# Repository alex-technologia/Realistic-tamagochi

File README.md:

# Realistic-tamagochi
A tamagochi but much more realistically accurate 
My parents have always been pretty negative about having a pet. To them i do not have the responsibility to keep one. Ive heard tamogochi before and tried to use it as a proof that i am a responsible person. But they still think its not releastic enough and till this day i dont have a pet. So this project is me tamogochi but much more accurate as having an actual pet. 

The tamagochi has the same playstyle as a normal tamagochi but i added a moisture and temperature sensor so that when you just threw somewhere like your bag it will die just like a real pet. I also made it so that you can make it stand on your table or any surfaces so that its easier to look at it. I also added a keychain hole for it so that its easier to bring around. 

I used a game character as a reference for building the case for the tamagochi because I would actually keep it as a pet. No kidding its cute af. 

So like a normal tamagochi you feed it everyday, but do not overfeed it or feed it too less, just like a real pet. Also you need to interact with twice a day so that it woudnt die of boredom. PS: just like a real pet does :D 

Schematic diagram 

PCB diagram 

BOM 	

Zine

Reference 
- Hatsune Soup
- Amogus

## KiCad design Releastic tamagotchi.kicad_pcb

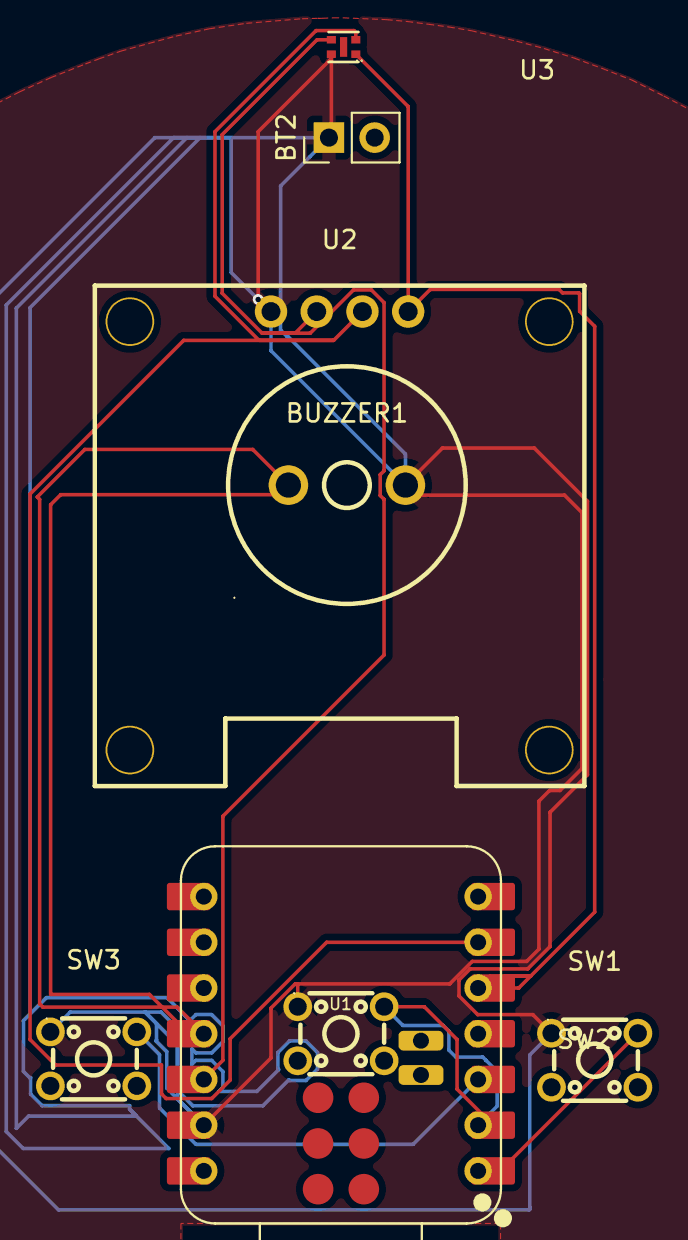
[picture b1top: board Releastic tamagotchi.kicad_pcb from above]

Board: 2 copper layers, 8 parts (0 on the bottom side), 8 nets.

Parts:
BT2: Battery_Cell; PinHeader_1x02_P2.54mm_Vertical
BUZZER1: 1207-P6.5MM; BUZ-TH_BD12.5-P6.50-D1.4
SW1, SW2, SW3: SW_Push; SW-TH_4P-L4.5-W4.5-P3.00-LS4.8
U1: XIAO-ESP32-C3-SMD; XIAO-ESP32-C3-DIP-SMD
U2: HS96L03W2C03; OLED-TH_L27.8-W27.2-P2.54_C9900033791
U3: SHT40-N-NF; DFN-4_L1.5-W1.5-P0.80-TL-EP

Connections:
+3V3: U1.12 (3V3), U2.2 (VCC), U3.3 (VDD)
GND: BT2.1 (+), BUZZER1.2 (-), SW1.1 (1_1), SW2.1 (1_1), SW3.1 (1_1), U1.13 (GND), U2.1 (GND), U3.4 (VSS)
unnamed: BUZZER1.1 (+), U1.11 (GPIO10_D10_MOSI)
unnamed: SW1.1 (2_2), U1.1 (GPIO2_A0_D0)
unnamed: SW2.1 (2_2), U1.2 (GPIO3_A1_D1)
unnamed: SW3.1 (2_2), U1.3 (GPIO4_A2_D2)
unnamed: U1.5 (GPIO6_D4_SDA), U2.4 (SDA), U3.1 (SDA)
unnamed: U1.6 (GPIO7_D5_SCL), U2.3 (SCL), U3.2 (SCL)

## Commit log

2026-05-30 Initial Commit
    Nothing yet
2026-06-10 Enhance README with project background and features
    Expanded project description and added details about features and functionality.
2026-06-11 Add BOM and Zine images to README
2026-06-11 Create CAD
2026-06-14 Add reference section to README
2026-06-14 Create Onshape link
